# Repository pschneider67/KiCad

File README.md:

# Platine KiCad Projekt - Power_3.3

Power_3.3 ist eine kleine Platine die aus 
240V AC - 3,3V DC / 3W 
macht.

Power_3.3 ist ein KiCad Projekt

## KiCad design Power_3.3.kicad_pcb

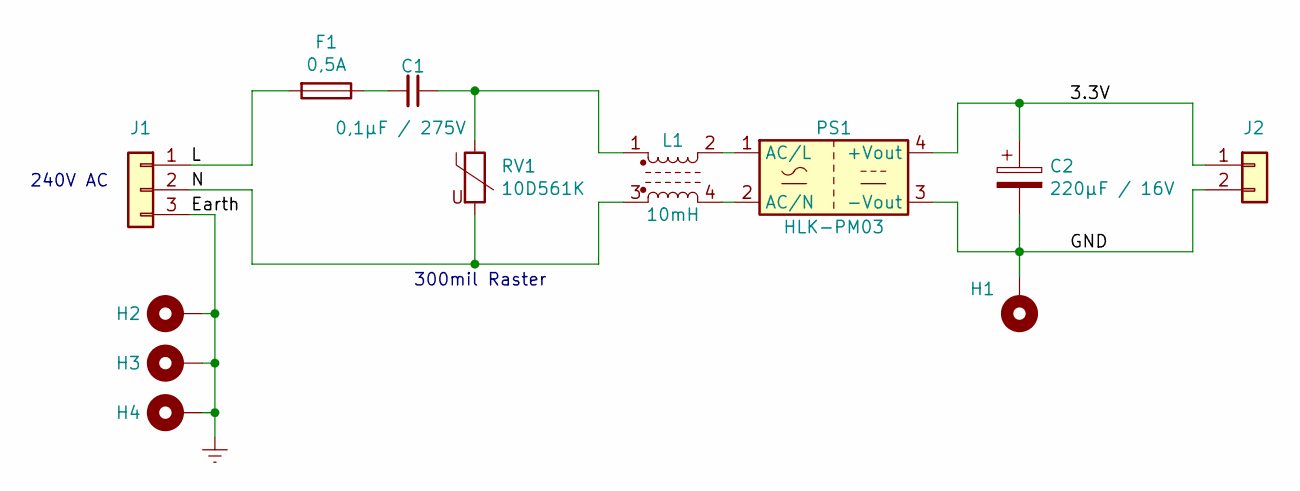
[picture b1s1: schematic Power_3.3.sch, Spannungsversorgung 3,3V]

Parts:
C1: 0,1µF / 275V; C_Rect_L13.5mm_W5.0mm_P10.00mm_FKS3_FKP3_MKS4
C2: 220µF / 16V; CP_Radial_D6.3mm_P2.50mm
F1: 0,5A; Fuseholder_Cylinder-5x20mm_Stelvio-Kontek_PTF78_Horizontal_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
H1, H2, H3, H4: MountingHole_Pad; MountingHole_3.2mm_M3_Pad
J1: Conn_01x03; PhoenixContact_MSTBVA_2,5_3-G-5,08_1x03_P5.08mm_Vertical
J2: Conn_01x02; PhoenixContact_MCV_1,5_2-G-3.5_1x02_P3.50mm_Vertical
L1: 10mH; Choke_Schaffner_RN112-04-17.7x17.1mm
PS1: HLK-PM03; Converter_ACDC_HiLink_HLK-PMxx
RV1: 10D561K; RV_Disc_D12mm_W7.5mm_P7.5mm

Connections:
/3.3V: C2.1, J2.1, PS1.4 (+Vout)
/GND: C2.2, H1.1, J2.2, PS1.3 (-Vout)
/L: F1.2, J1.1
/N: J1.2, L1.3, RV1.2
Earth: H2.1, H3.1, H4.1, J1.3
unnamed: C1.1, L1.1, RV1.1
unnamed: C1.2, F1.1
unnamed: L1.2, PS1.1 (AC/L)
unnamed: L1.4, PS1.2 (AC/N)

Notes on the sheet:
300mil Raster
240V AC

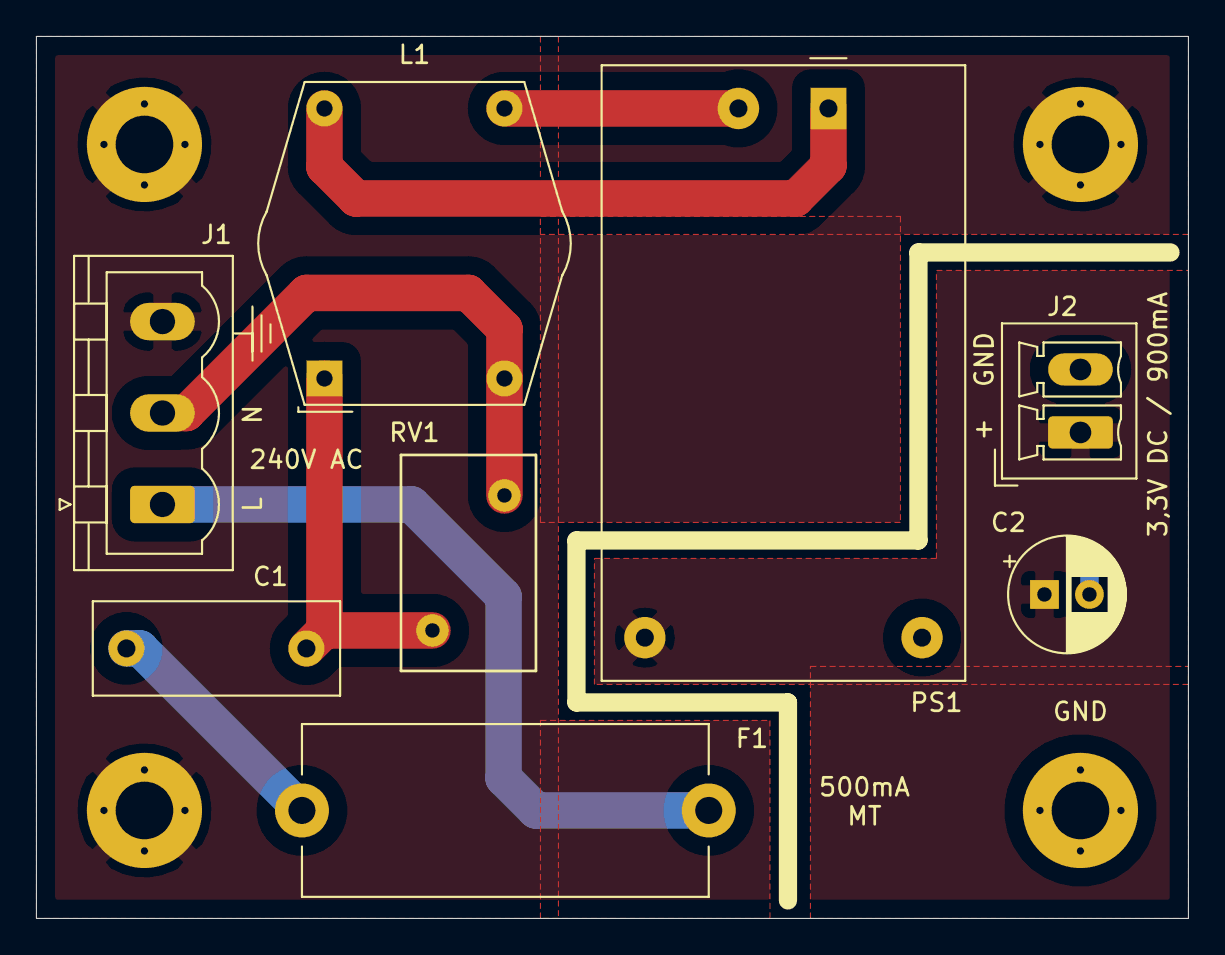
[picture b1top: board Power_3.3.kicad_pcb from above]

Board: 2 copper layers, 64.0 x 49.0 mm, 12 parts (0 on the bottom side), 9 nets.

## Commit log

2021-11-04 Start Power_3.3
2021-11-05 Kupferflächen neu erstellt
2021-11-05 neue Plazireung der Bauteile
2021-11-19 Kleinere Änderrungen
